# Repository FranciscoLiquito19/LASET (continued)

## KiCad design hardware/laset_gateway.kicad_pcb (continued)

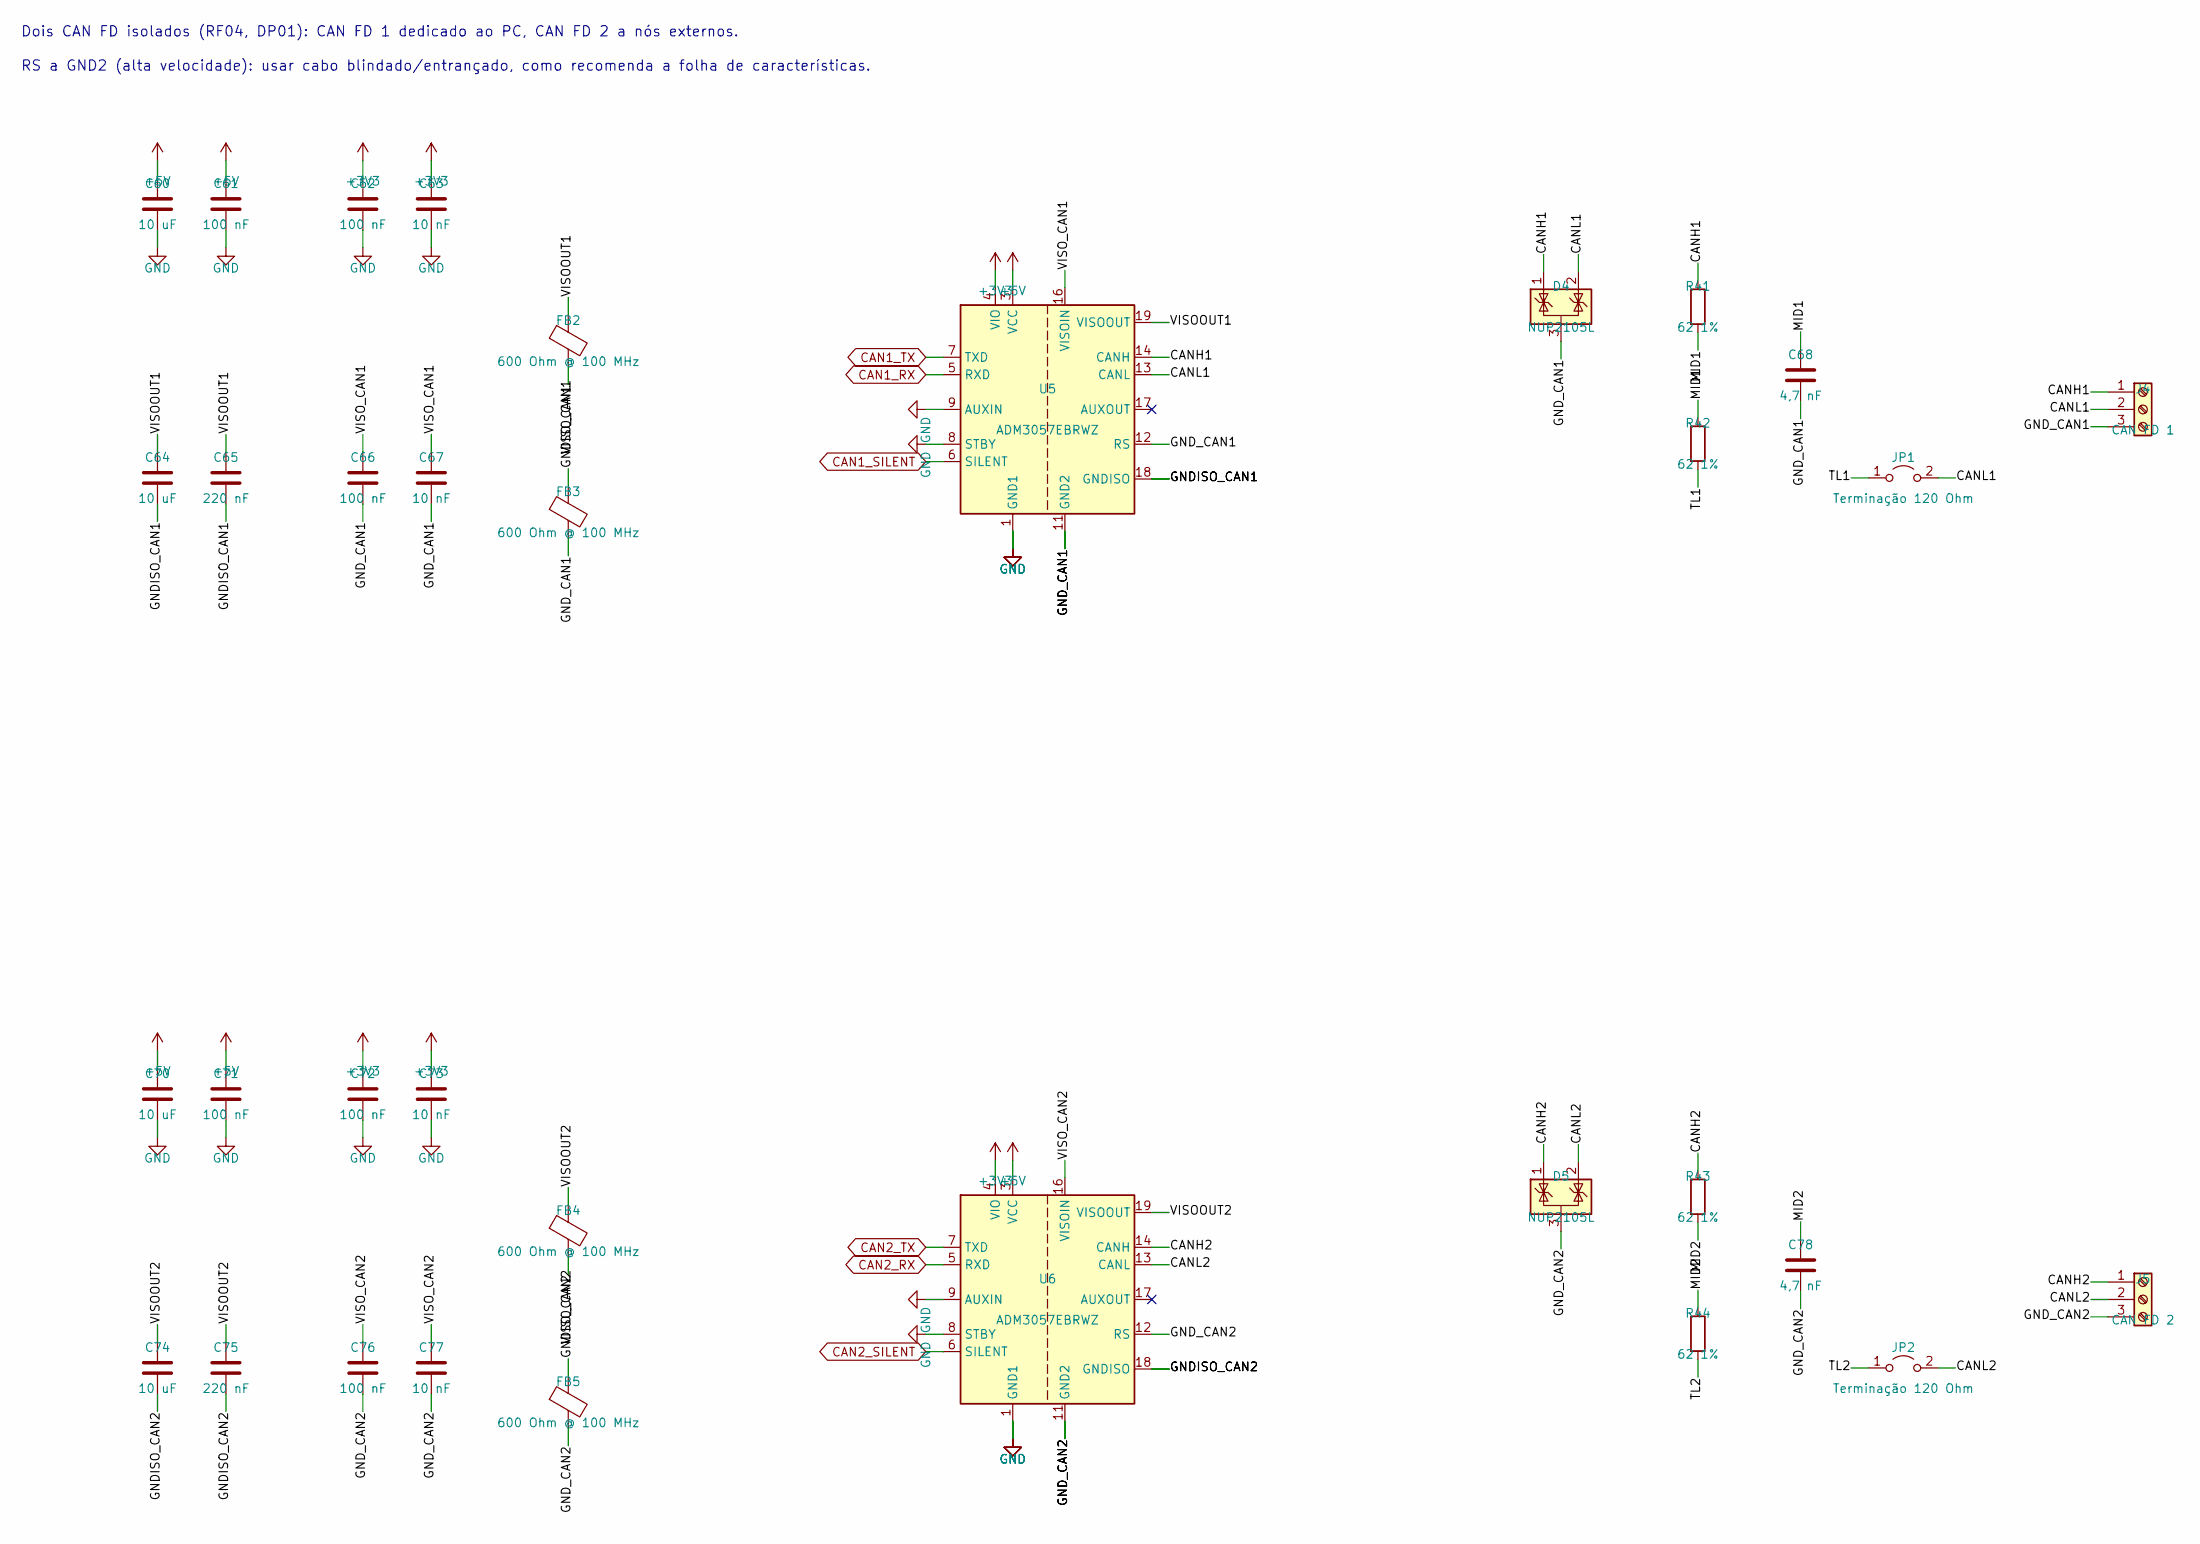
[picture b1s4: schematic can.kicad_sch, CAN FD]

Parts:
C60, C64, C70, C74: 10 uF; C_1206_3216Metric
C61, C62, C66, C71, C72, C76: 100 nF; C_0603_1608Metric
C63, C67, C73, C77: 10 nF; C_0603_1608Metric
C65, C75: 220 nF; C_0603_1608Metric
C68, C78: 4,7 nF; C_0603_1608Metric
D4, D5: NUP2105L; SOT-23
FB2, FB3, FB4, FB5: 600 Ohm @ 100 MHz; L_0603_1608Metric
J4: CAN FD 1; TerminalBlock_Phoenix_MKDS-1,5-3_1x03_P5.00mm_Horizontal
J5: CAN FD 2; TerminalBlock_Phoenix_MKDS-1,5-3_1x03_P5.00mm_Horizontal
JP1, JP2: Terminação 120 Ohm; PinHeader_1x02_P2.54mm_Vertical
R41, R42, R43, R44: 62 1%; R_0603_1608Metric
U5, U6: ADM3057EBRWZ; SOIC-20W_7.5x12.8mm_P1.27mm

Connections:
+3V3: C62.1, C63.1, C72.1, C73.1, U5.4 (VIO), U6.4 (VIO); also elsewhere on the board
+5V: C60.1, C61.1, C70.1, C71.1, U5.3 (VCC), U6.3 (VCC); also elsewhere on the board
/CAN FD/CANH1: D4.1 (K), J4.1, R41.1, U5.14 (CANH)
/CAN FD/CANH2: D5.1 (K), J5.1, R43.1, U6.14 (CANH)
/CAN FD/CANL1: D4.2 (K), J4.2, JP1.2 (B), U5.13 (CANL)
/CAN FD/CANL2: D5.2 (K), J5.2, JP2.2 (B), U6.13 (CANL)
/CAN FD/GNDISO_CAN1: C64.2, C65.2, FB3.1, U5.18 (GNDISO), U5.20 (GNDISO)
/CAN FD/GNDISO_CAN2: C74.2, C75.2, FB5.1, U6.18 (GNDISO), U6.20 (GNDISO)
/CAN FD/GND_CAN1: C66.2, C67.2, C68.2, D4.3 (A), FB3.2, J4.3, U5.11 (GND2), U5.12 (RS), U5.15 (GND2)
/CAN FD/GND_CAN2: C76.2, C77.2, C78.2, D5.3 (A), FB5.2, J5.3, U6.11 (GND2), U6.12 (RS), U6.15 (GND2)
/CAN FD/MID1: C68.1, R41.2, R42.1
/CAN FD/MID2: C78.1, R43.2, R44.1
/CAN FD/TL1: JP1.1 (A), R42.2
/CAN FD/TL2: JP2.1 (A), R44.2
/CAN FD/VISOOUT1: C64.1, C65.1, FB2.1, U5.19 (VISOOUT)
/CAN FD/VISOOUT2: C74.1, C75.1, FB4.1, U6.19 (VISOOUT)
/CAN FD/VISO_CAN1: C66.1, C67.1, FB2.2, U5.16 (VISOIN)
/CAN FD/VISO_CAN2: C76.1, C77.1, FB4.2, U6.16 (VISOIN)
CAN1_RX: U5.5 (RXD); also elsewhere on the board
CAN1_SILENT: U5.6 (SILENT); also elsewhere on the board
CAN1_TX: U5.7 (TXD); also elsewhere on the board
CAN2_RX: U6.5 (RXD); also elsewhere on the board
CAN2_SILENT: U6.6 (SILENT); also elsewhere on the board
CAN2_TX: U6.7 (TXD); also elsewhere on the board
GND: C60.2, C61.2, C62.2, C63.2, C70.2, C71.2, C72.2, C73.2, U5.1 (GND1), U5.2 (GND1), U5.8 (STBY), U5.9 (AUXIN), U5.10 (GND1), U6.1 (GND1), U6.2 (GND1), U6.8 (STBY), U6.9 (AUXIN), U6.10 (GND1); also elsewhere on the board

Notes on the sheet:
Dois CAN FD isolados (RF04, DP01): CAN FD 1 dedicado ao PC, CAN FD 2 a nós externos.
RS a GND2 (alta velocidade): usar cabo blindado/entrançado, como recomenda a folha de características.

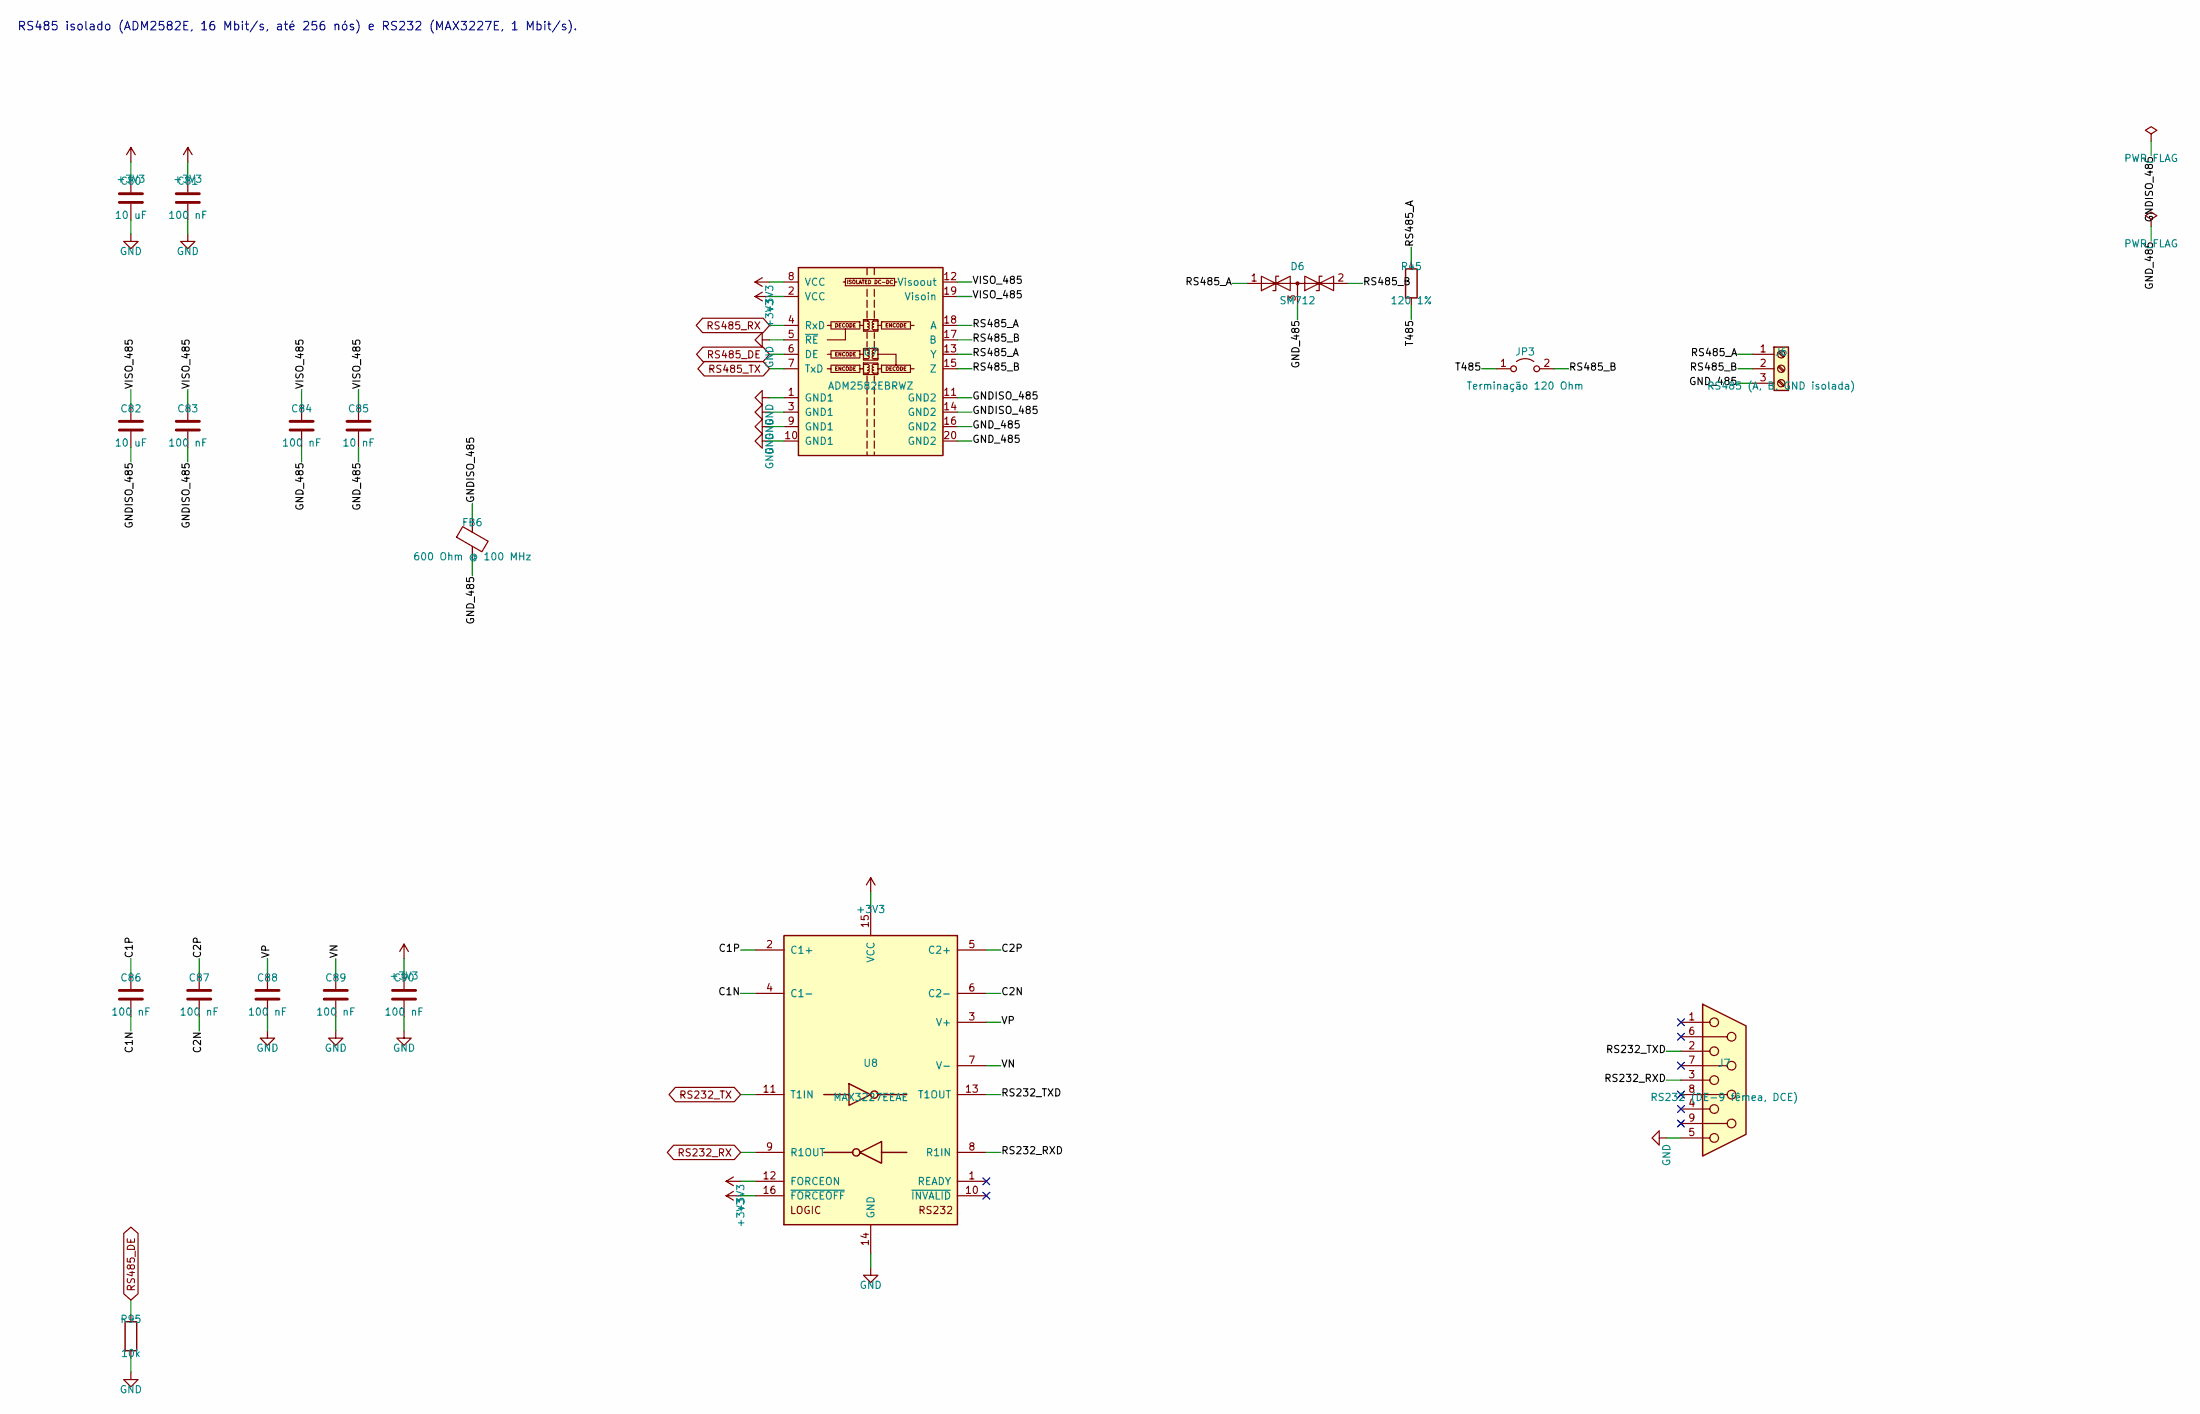
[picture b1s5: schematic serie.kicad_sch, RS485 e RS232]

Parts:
C80, C82: 10 uF; C_1206_3216Metric
C81, C83, C84, C86, C87, C88, C89, C90: 100 nF; C_0603_1608Metric
C85: 10 nF; C_0603_1608Metric
D6: SM712; SOT-23
FB6: 600 Ohm @ 100 MHz; L_0603_1608Metric
J6: RS485 (A, B, GND isolada); TerminalBlock_Phoenix_MKDS-1,5-3_1x03_P5.00mm_Horizontal
J7: RS232 (DE-9 fêmea, DCE); DSUB-9_Female_Horizontal_P2.77x2.84mm_EdgePinOffset7.70mm_H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
JP3: Terminação 120 Ohm; PinHeader_1x02_P2.54mm_Vertical
R45: 120 1%; R_0603_1608Metric
R95: 10k; R_0603_1608Metric
U7: ADM2582EBRWZ; SOIC-20W_7.5x12.8mm_P1.27mm
U8: MAX3227EEAE; SSOP-16_5.3x6.2mm_P0.65mm

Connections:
+3V3: C80.1, C81.1, C90.1, U7.2 (VCC), U7.8 (VCC), U8.12 (FORCEON), U8.15 (VCC), U8.16 (~FORCEOFF); also elsewhere on the board
/RS485 e RS232/C1N: C86.2, U8.4 (C1-)
/RS485 e RS232/C1P: C86.1, U8.2 (C1+)
/RS485 e RS232/C2N: C87.2, U8.6 (C2-)
/RS485 e RS232/C2P: C87.1, U8.5 (C2+)
/RS485 e RS232/GNDISO_485: C82.2, C83.2, FB6.1, U7.11 (GND2), U7.14 (GND2)
/RS485 e RS232/GND_485: C84.2, C85.2, D6.3 (common), FB6.2, J6.3, U7.16 (GND2), U7.20 (GND2)
/RS485 e RS232/RS232_RXD: J7.3, U8.8 (R1IN)
/RS485 e RS232/RS232_TXD: J7.2, U8.13 (T1OUT)
/RS485 e RS232/RS485_A: D6.1 (A1), J6.1, R45.1, U7.13 (Y), U7.18 (A)
/RS485 e RS232/RS485_B: D6.2 (A2), J6.2, JP3.2 (B), U7.15 (Z), U7.17 (B)
/RS485 e RS232/T485: JP3.1 (A), R45.2
/RS485 e RS232/VISO_485: C82.1, C83.1, C84.1, C85.1, U7.12 (Visoout), U7.19 (Visoin)
/RS485 e RS232/VN: C89.1, U8.7 (V-)
/RS485 e RS232/VP: C88.1, U8.3 (V+)
GND: C80.2, C81.2, C88.2, C89.2, C90.2, J7.5, R95.2, U7.1 (GND1), U7.3 (GND1), U7.5 (~RE), U7.9 (GND1), U7.10 (GND1), U8.14 (GND); also elsewhere on the board
RS232_RX: U8.9 (R1OUT); also elsewhere on the board
RS232_TX: U8.11 (T1IN); also elsewhere on the board
RS485_DE: R95.1, U7.6 (DE); also elsewhere on the board
RS485_RX: U7.4 (RxD); also elsewhere on the board
RS485_TX: U7.7 (TxD); also elsewhere on the board

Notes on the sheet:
RS485 isolado (ADM2582E, 16 Mbit/s, até 256 nós) e RS232 (MAX3227E, 1 Mbit/s).

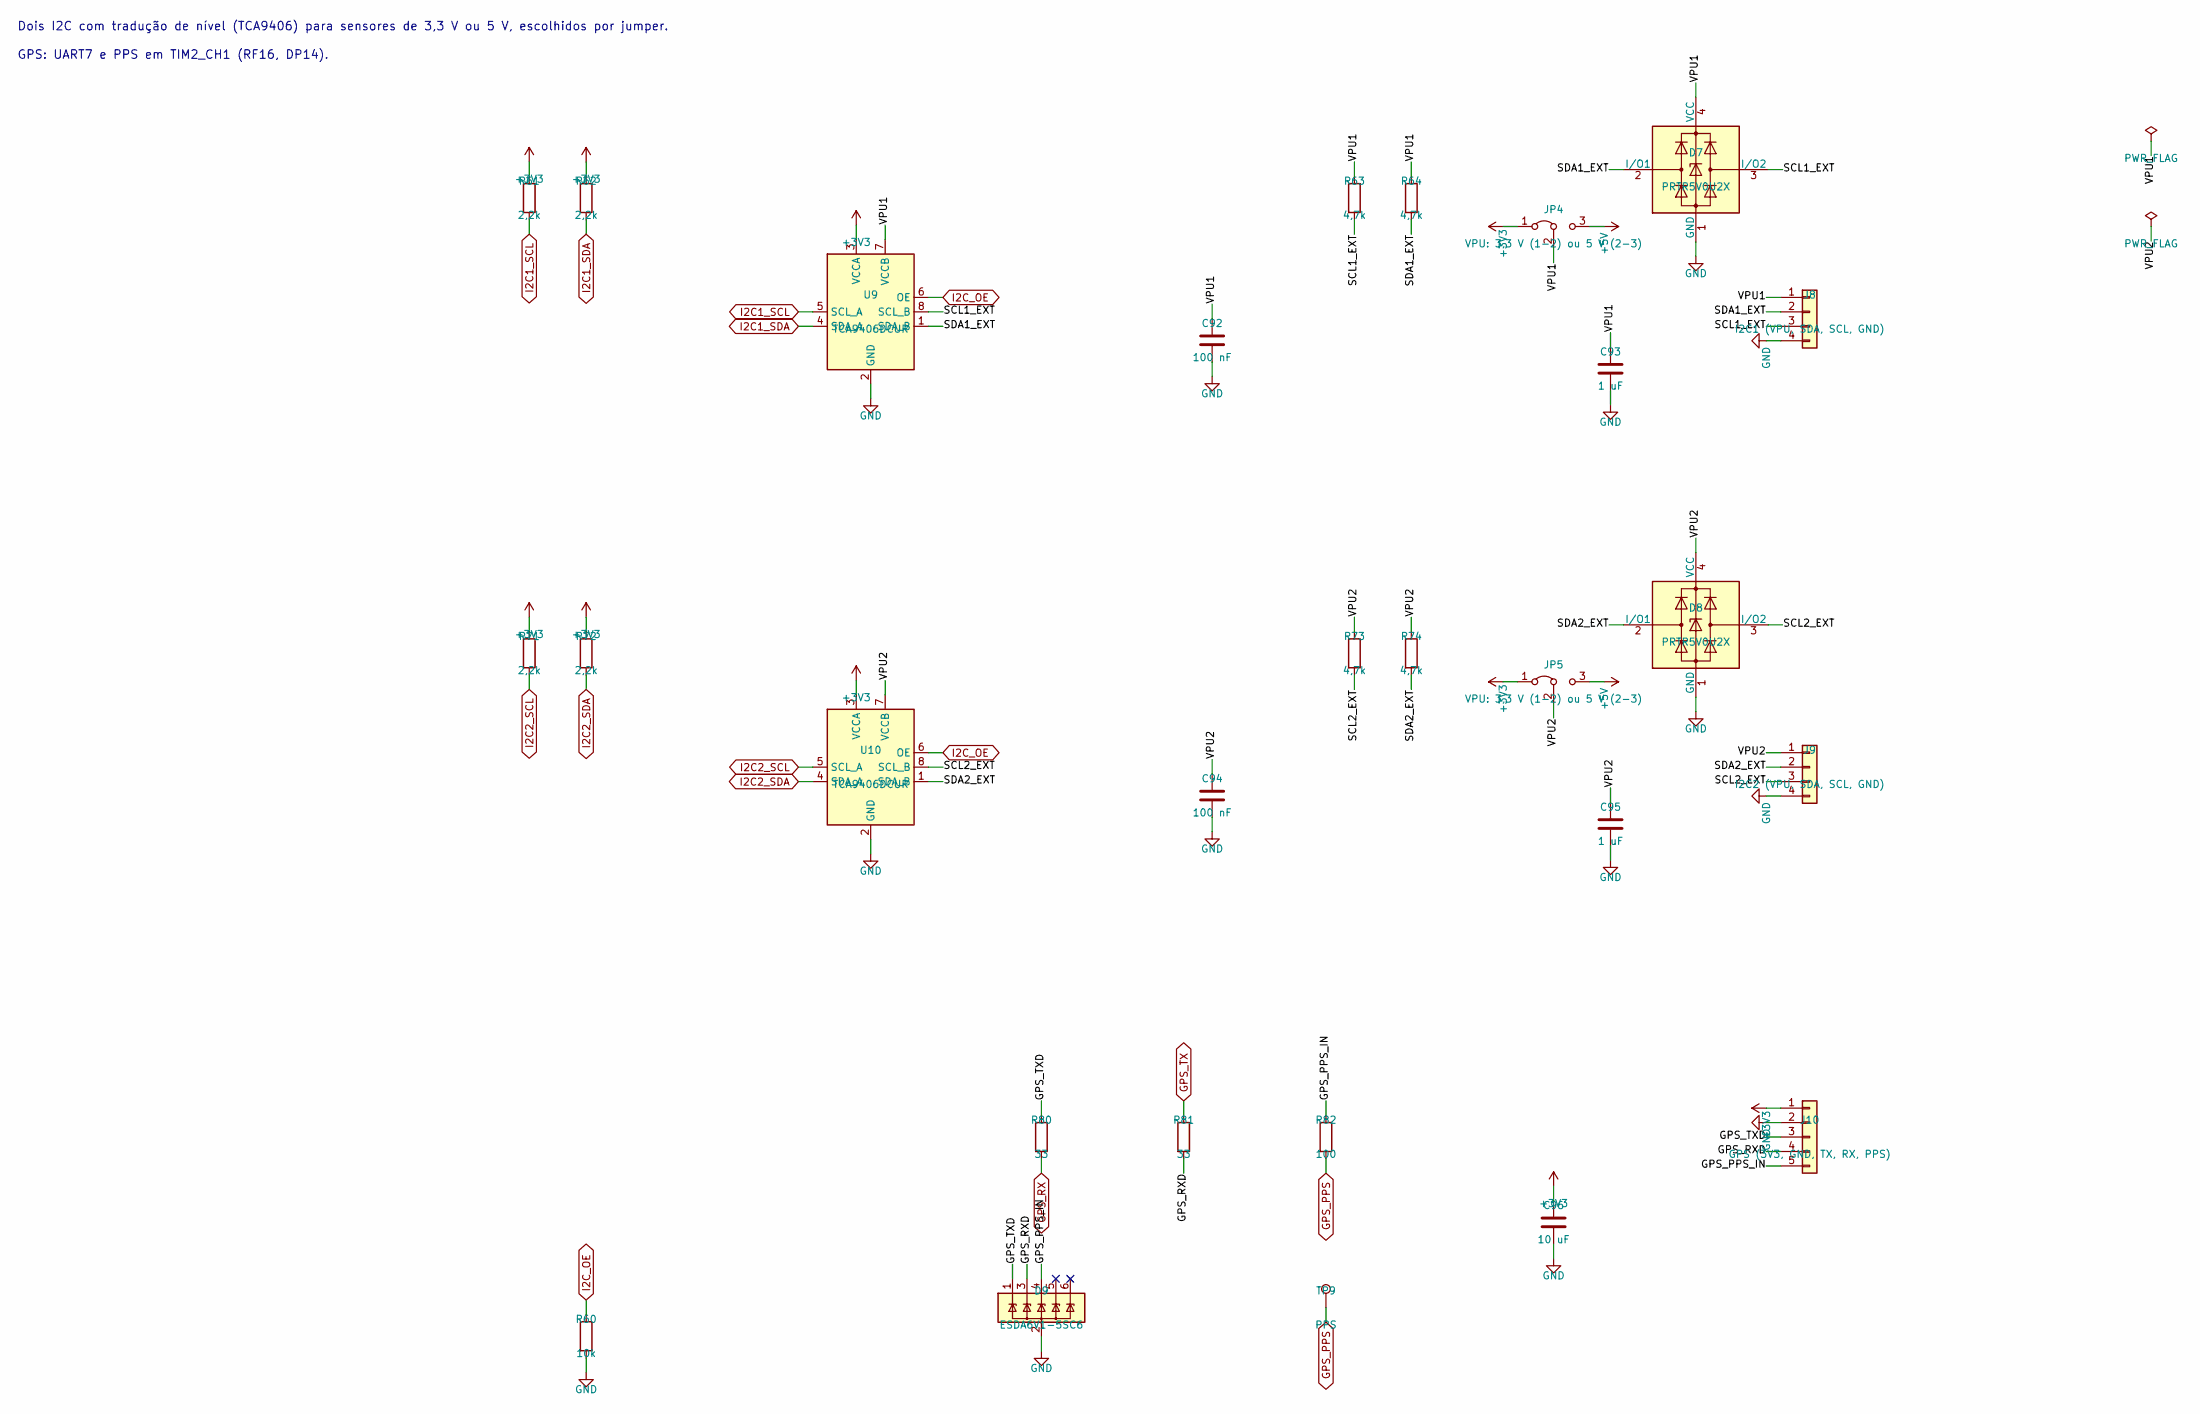
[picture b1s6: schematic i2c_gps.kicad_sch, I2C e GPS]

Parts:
C92, C94: 100 nF; C_0603_1608Metric
C93, C95: 1 uF; C_0603_1608Metric
C96: 10 uF; C_1206_3216Metric
D7, D8: PRTR5V0U2X; SOT-143
D9: ESDA6V1-5SC6; SOT-23-6
J8: I2C1 (VPU, SDA, SCL, GND); JST_PH_B4B-PH-K_1x04_P2.00mm_Vertical
J9: I2C2 (VPU, SDA, SCL, GND); JST_PH_B4B-PH-K_1x04_P2.00mm_Vertical
J10: GPS (3V3, GND, TX, RX, PPS); JST_PH_B5B-PH-K_1x05_P2.00mm_Vertical
JP4, JP5: VPU: 3,3 V (1-2) ou 5 V (2-3); PinHeader_1x03_P2.54mm_Vertical
R60: 10k; R_0603_1608Metric
R61, R62, R71, R72: 2,2k; R_0603_1608Metric
R63, R64, R73, R74: 4,7k; R_0603_1608Metric
R80, R81: 33; R_0603_1608Metric
R82: 100; R_0603_1608Metric
TP9: PPS; TestPoint_Pad_D1.5mm
U9, U10: TCA9406DCUR; VSSOP-8_2.3x2mm_P0.5mm

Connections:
+3V3: C96.1, J10.1, JP4.1 (A), JP5.1 (A), R61.1, R62.1, R71.1, R72.1, U9.3 (VCCA), U10.3 (VCCA); also elsewhere on the board
+5V: JP4.3 (B), JP5.3 (B); also elsewhere on the board
/I2C e GPS/GPS_PPS_IN: D9.4 (IO3), J10.5, R82.1
/I2C e GPS/GPS_RXD: D9.3 (IO2), J10.4, R81.2
/I2C e GPS/GPS_TXD: D9.1 (IO1), J10.3, R80.1
/I2C e GPS/SCL1_EXT: D7.3 (I/O2), J8.3, R63.2, U9.8 (SCL_B)
/I2C e GPS/SCL2_EXT: D8.3 (I/O2), J9.3, R73.2, U10.8 (SCL_B)
/I2C e GPS/SDA1_EXT: D7.2 (I/O1), J8.2, R64.2, U9.1 (SDA_B)
/I2C e GPS/SDA2_EXT: D8.2 (I/O1), J9.2, R74.2, U10.1 (SDA_B)
/I2C e GPS/VPU1: C92.1, C93.1, D7.4 (VCC), J8.1, JP4.2 (C), R63.1, R64.1, U9.7 (VCCB)
/I2C e GPS/VPU2: C94.1, C95.1, D8.4 (VCC), J9.1, JP5.2 (C), R73.1, R74.1, U10.7 (VCCB)
GND: C92.2, C93.2, C94.2, C95.2, C96.2, D7.1 (GND), D8.1 (GND), D9.2 (GND), J8.4, J9.4, J10.2, R60.2, U9.2 (GND), U10.2 (GND); also elsewhere on the board
GPS_PPS: R82.2, TP9.1; also elsewhere on the board
GPS_RX: R80.2; also elsewhere on the board
GPS_TX: R81.1; also elsewhere on the board
I2C1_SCL: R61.2, U9.5 (SCL_A); also elsewhere on the board
I2C1_SDA: R62.2, U9.4 (SDA_A); also elsewhere on the board
I2C2_SCL: R71.2, U10.5 (SCL_A); also elsewhere on the board
I2C2_SDA: R72.2, U10.4 (SDA_A); also elsewhere on the board
I2C_OE: R60.1, U9.6 (OE), U10.6 (OE); also elsewhere on the board

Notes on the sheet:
Dois I2C com tradução de nível (TCA9406) para sensores de 3,3 V ou 5 V, escolhidos por jumper.
GPS: UART7 e PPS em TIM2_CH1 (RF16, DP14).

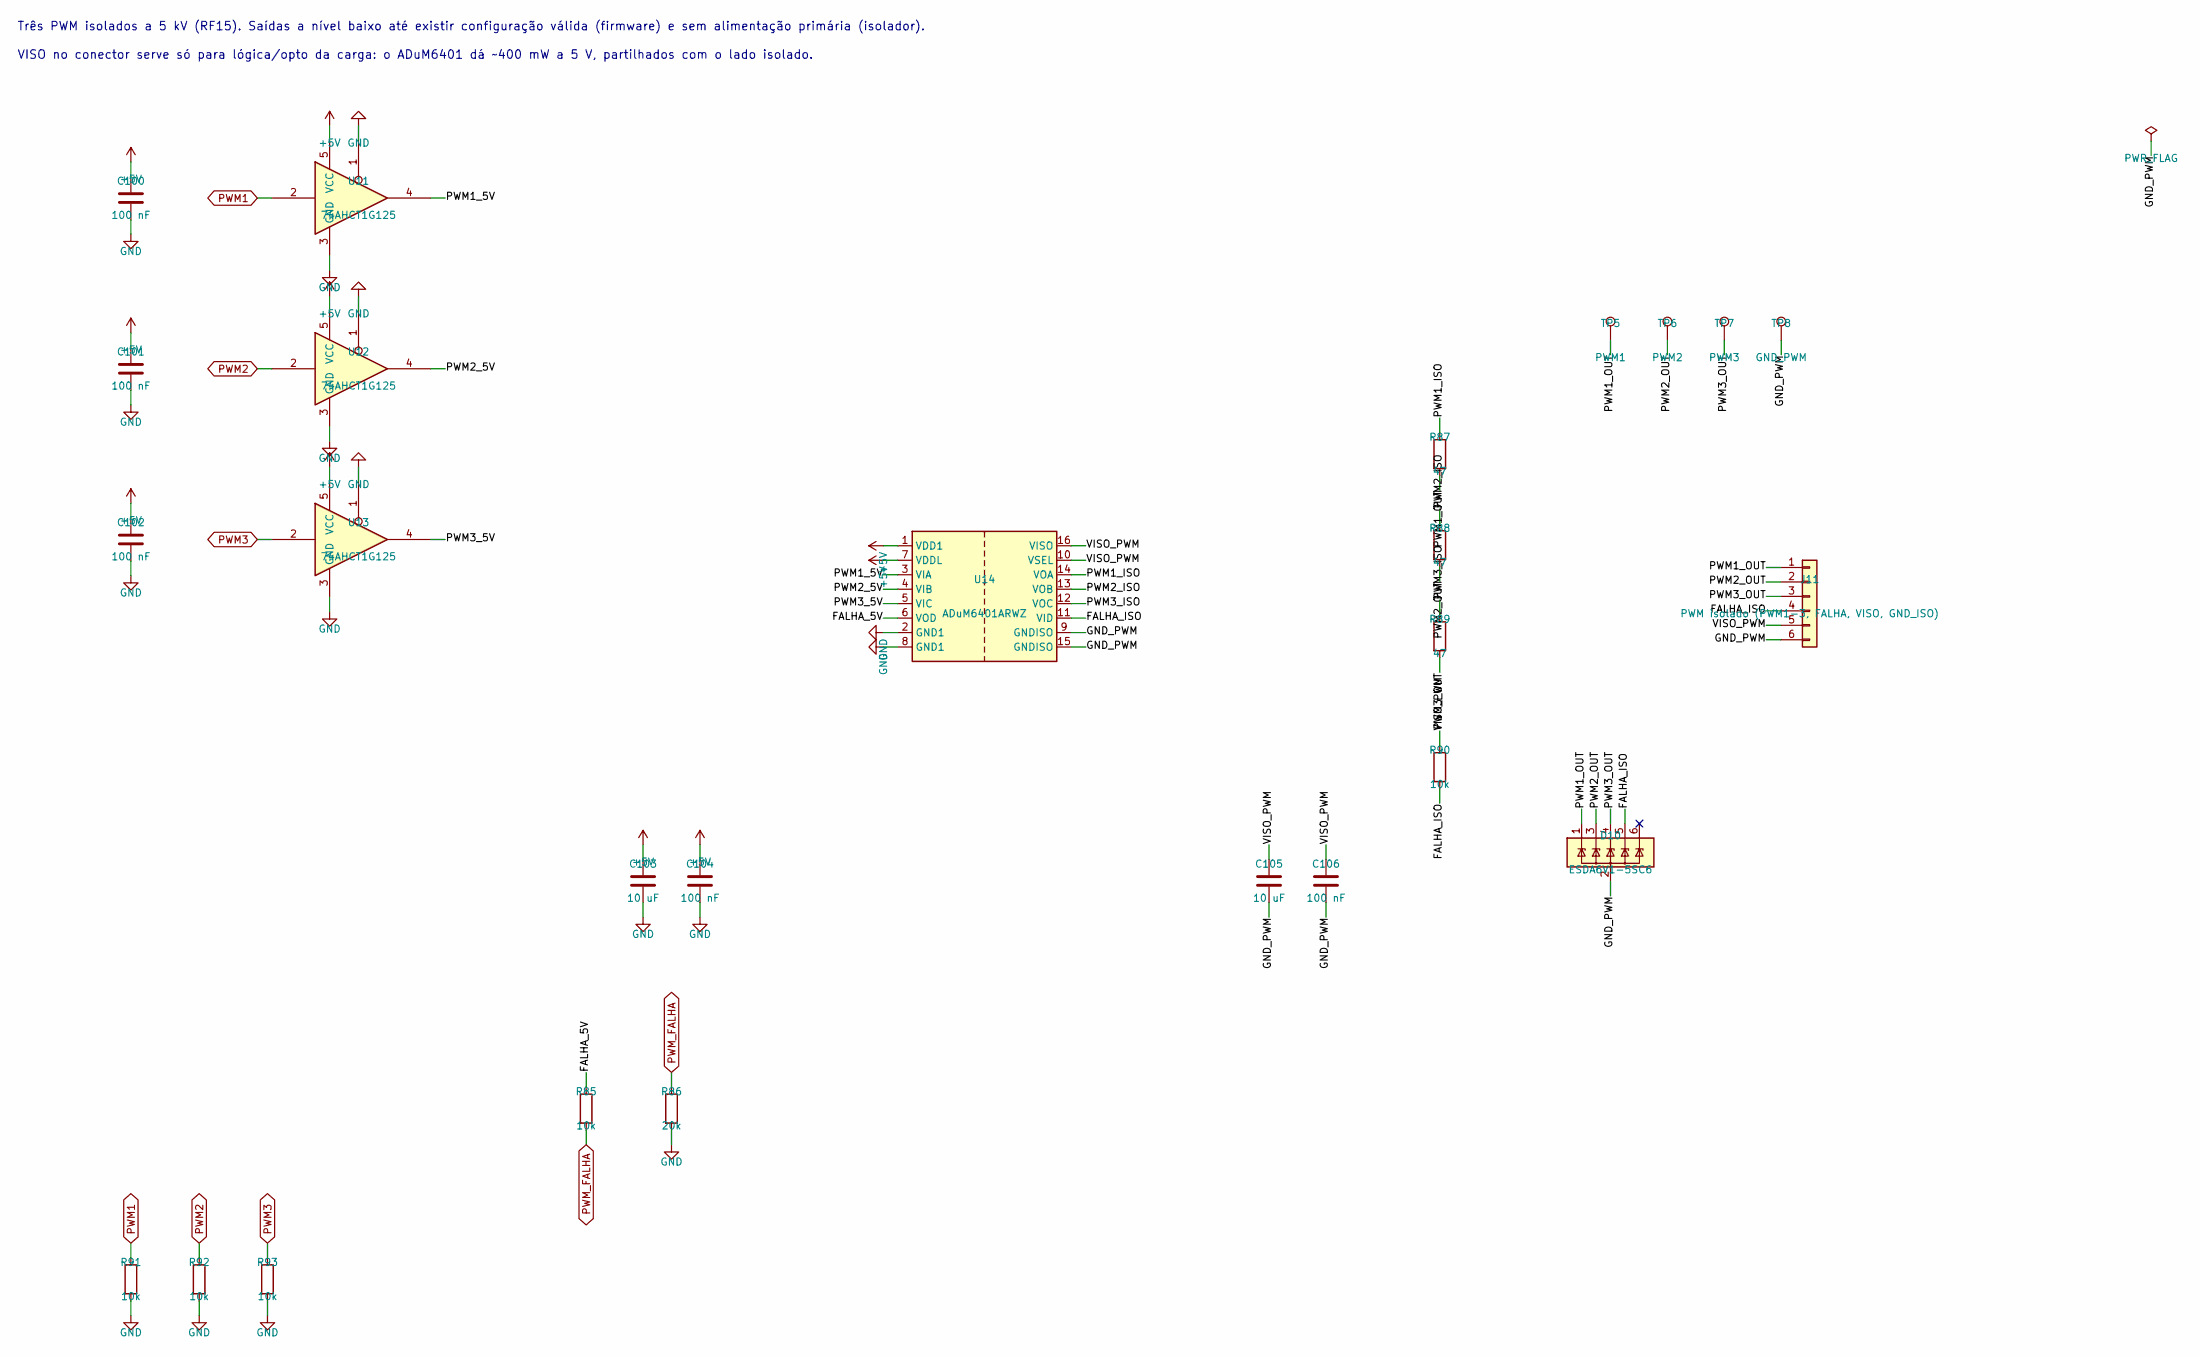
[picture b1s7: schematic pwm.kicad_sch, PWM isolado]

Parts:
C100, C101, C102, C104, C106: 100 nF; C_0603_1608Metric
C103, C105: 10 uF; C_1206_3216Metric
D10: ESDA6V1-5SC6; SOT-23-6
J11: PWM isolado (PWM1-3, FALHA, VISO, GND_ISO); JST_PH_B6B-PH-K_1x06_P2.00mm_Vertical
R85, R90, R91, R92, R93: 10k; R_0603_1608Metric
R86: 20k; R_0603_1608Metric
R87, R88, R89: 47; R_0603_1608Metric
TP5: PWM1; TestPoint_Pad_D1.5mm
TP6: PWM2; TestPoint_Pad_D1.5mm
TP7: PWM3; TestPoint_Pad_D1.5mm
TP8: GND_PWM; TestPoint_Pad_D1.5mm
U11, U12, U13: 74AHCT1G125; SOT-23-5
U14: ADuM6401ARWZ; SOIC-16W_7.5x10.3mm_P1.27mm

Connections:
+5V: C100.1, C101.1, C102.1, C103.1, C104.1, U11.5 (VCC), U12.5 (VCC), U13.5 (VCC), U14.1 (VDD1), U14.7 (VDDL); also elsewhere on the board
/PWM isolado/FALHA_5V: R85.1, U14.6 (VOD)
/PWM isolado/FALHA_ISO: D10.5 (IO4), J11.4, R90.2, U14.11 (VID)
/PWM isolado/GND_PWM: C105.2, C106.2, D10.2 (GND), J11.6, TP8.1, U14.9 (GNDISO), U14.15 (GNDISO)
/PWM isolado/PWM1_5V: U11.4, U14.3 (VIA)
/PWM isolado/PWM1_ISO: R87.1, U14.14 (VOA)
/PWM isolado/PWM1_OUT: D10.1 (IO1), J11.1, R87.2, TP5.1
/PWM isolado/PWM2_5V: U12.4, U14.4 (VIB)
/PWM isolado/PWM2_ISO: R88.1, U14.13 (VOB)
/PWM isolado/PWM2_OUT: D10.3 (IO2), J11.2, R88.2, TP6.1
/PWM isolado/PWM3_5V: U13.4, U14.5 (VIC)
/PWM isolado/PWM3_ISO: R89.1, U14.12 (VOC)
/PWM isolado/PWM3_OUT: D10.4 (IO3), J11.3, R89.2, TP7.1
/PWM isolado/VISO_PWM: C105.1, C106.1, J11.5, R90.1, U14.10 (VSEL), U14.16 (VISO)
GND: C100.2, C101.2, C102.2, C103.2, C104.2, R86.2, R91.2, R92.2, R93.2, U11.1, U11.3 (GND), U12.1, U12.3 (GND), U13.1, U13.3 (GND), U14.2 (GND1), U14.8 (GND1); also elsewhere on the board
PWM1: R91.1, U11.2; also elsewhere on the board
PWM2: R92.1, U12.2; also elsewhere on the board
PWM3: R93.1, U13.2; also elsewhere on the board
PWM_FALHA: R85.2, R86.1; also elsewhere on the board

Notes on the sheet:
Três PWM isolados a 5 kV (RF15). Saídas a nível baixo até existir configuração válida (firmware) e sem alimentação primária (isolador).
VISO no conector serve só para lógica/opto da carga: o ADuM6401 dá ~400 mW a 5 V, partilhados com o lado isolado.

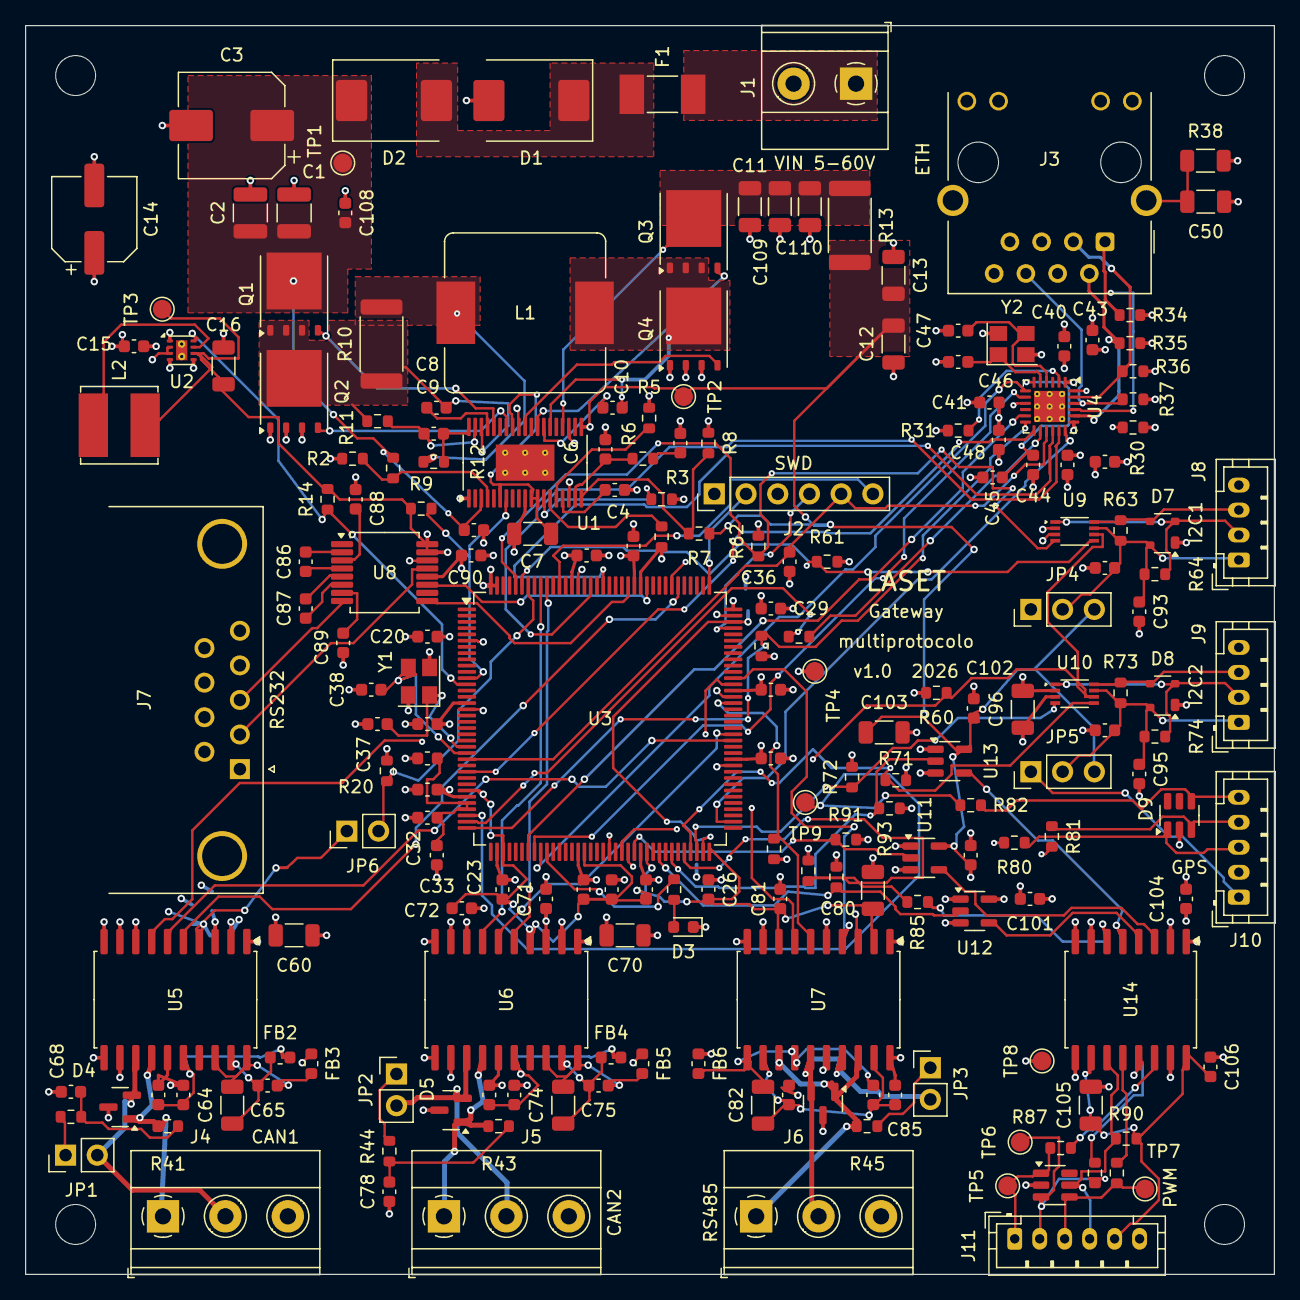
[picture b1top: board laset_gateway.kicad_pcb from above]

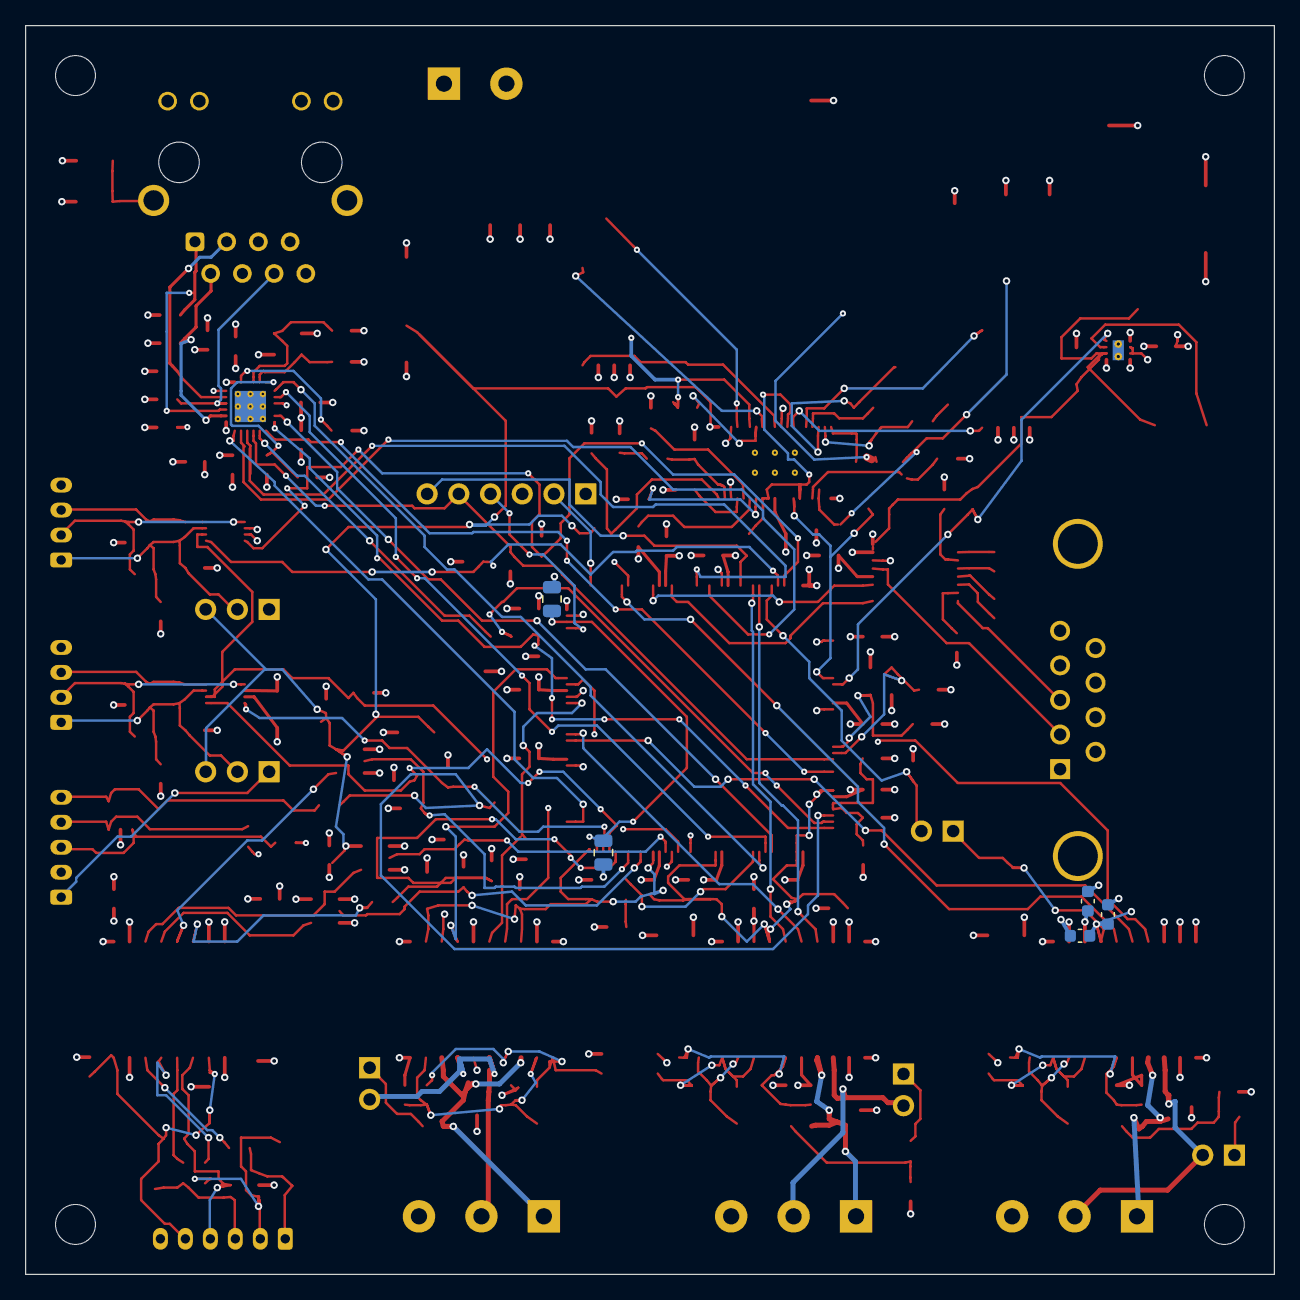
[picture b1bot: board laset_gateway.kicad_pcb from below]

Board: 4 copper layers, 100.0 x 100.0 mm, 212 parts (5 on the bottom side), 136 nets.

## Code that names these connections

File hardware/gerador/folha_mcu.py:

"""Folha 2: microcontrolador STM32H743ZIT6 (LQFP-144).

Atribuição de pinos (funções alternativas da folha de características DS12110 da ST;
o percurso Ethernet RMII é o mesmo da NUCLEO-H743ZI, o que permite reaproveitar o
projeto CubeMX da placa de avaliação):

  Ethernet RMII  PA1 REF_CLK, PA2 MDIO, PC1 MDC, PA7 CRS_DV, PC4 RXD0, PC5 RXD1,
                 PG11 TX_EN, PG13 TXD0, PB13 TXD1
  FDCAN1         PD0 RX, PD1 TX          SILENT do transceiver: PG2
  FDCAN2         PB5 RX, PB6 TX          SILENT do transceiver: PG3
  RS232 (USART2) PD5 TX, PD6 RX
  RS485 (USART6) PC6 TX, PC7 RX, PG8 DE (controlo automático do emissor)
  GPS (UART7)    PE8 TX, PE7 RX; PPS em PA0 = TIM2_CH1 (temporizador de 32 bits)
  I2C1           PB8 SCL, PB9 SDA
  I2C2           PB10 SCL, PB11 SDA (canto inferior direito, do lado dos conectores I2C)
  PWM (TIM1)     PE9 CH1, PE11 CH2, PE13 CH3; PE15 = TIM1_BKIN (falha isolada)
  SWD            PA13 SWDIO, PA14 SWCLK, PB3 SWO
  Estado         PB0 LED; PF2 PG_5V; PF3 PG_3V3
"""
from hw import Folha, simbolo, pinos
from comum import (R, C, FB, R0603, C0603, C0805, FB0603, LED0603, XTAL3225, JP2, desacoplamento)

MCU = 'MCU_ST_STM32H7:STM32H743ZITx'

PINOS = {
    # alimentação
    'VDD': '+3V3', 'VDD33_USB': '+3V3', 'VBAT': '+3V3', 'VSS': 'GND', 'VSSA': 'GND',
    # PDR_ON a VDD liga o supervisor interno (reset por queda de tensão), como na NUCLEO;
    # flutuante fica indefinido.
    'PDR_ON': '+3V3',
    'VDDA': '/VDDA', 'VREF+': '/VDDA', 'VCAP': '/VCAP', 'NRST': 'NRST', 'BOOT0': '/BOOT0',
    'PH0': '/OSC_IN', 'PH1': '/OSC_OUT',
    # Ethernet RMII
    'PA1': 'ETH_REF_CLK', 'PA2': 'ETH_MDIO', 'PC1': 'ETH_MDC', 'PA7': 'ETH_CRS_DV',
    'PC4': 'ETH_RXD0', 'PC5': 'ETH_RXD1', 'PG11': 'ETH_TX_EN', 'PG13': 'ETH_TXD0', 'PB13': 'ETH_TXD1',
    # CAN FD
    'PD0': 'CAN1_RX', 'PD1': 'CAN1_TX', 'PG2': 'CAN1_SILENT',
    'PB5': 'CAN2_RX', 'PB6': 'CAN2_TX', 'PG3': 'CAN2_SILENT',
    # série
    'PD5': 'RS232_TX', 'PD6': 'RS232_RX',
    'PC6': 'RS485_TX', 'PC7': 'RS485_RX', 'PG8': 'RS485_DE',
    # GPS
    'PE8': 'GPS_TX', 'PE7': 'GPS_RX', 'PA0': 'GPS_PPS',
    # I2C
    'PB8': 'I2C1_SCL', 'PB9': 'I2C1_SDA', 'PB10': 'I2C2_SCL', 'PB11': 'I2C2_SDA', 'PG0': 'I2C_OE',
    # PWM
    'PE9': 'PWM1', 'PE11': 'PWM2', 'PE13': 'PWM3', 'PE15': 'PWM_FALHA',
    # depuração e estado
    'PA13': '/SWDIO', 'PA14': '/SWCLK', 'PB3': '/SWO', 'PB0': '/LED',
    'PF2': 'PG_5V', 'PF3': 'PG_3V3',
}


def folha():
    f = Folha('Microcontrolador', 'mcu.kicad_sch', notas=[
        'STM32H743ZIT6 (DP03). Atribuição de pinos no cabeçalho de gerador/folha_mcu.py; os GPIO livres ficam marcados como não ligados.',
        'Condensadores de 100 nF junto a cada par VDD/VSS; VCAP com 2,2 uF de baixa ESR (< 100 mOhm) por pino.',
        'Cristal HSE de 25 MHz: condensadores de carga para C_L = 10 pF; ajustar se o cristal escolhido tiver outra C_L.',
    ])
    nomes = {p.name for p in pinos(simbolo(MCU))}
    for k in PINOS:
        assert k in nomes, k
    f.comp('U3', MCU, 'STM32H743ZIT6', 210, 150, PINOS, nc_resto=True)

    # Desacoplamento do domínio digital: um 100 nF por pino VDD + 4,7 uF de reserva
    refs = [f'C{20 + i}' for i in range(12)]
    desacoplamento(f, refs, ['100 nF'] * 11 + ['4,7 uF'], '+3V3', 'GND', 30, 40, passo=9)

    # VDDA e VREF+ filtrados
    f.comp('FB1', FB, '600 Ohm @ 100 MHz', 40, 80, {1: '+3V3', 2: '/VDDA'}, FB0603)
    f.comp('C32', C, '1 uF', 55, 80, {1: '/VDDA', 2: 'GND'}, C0603)
    f.comp('C33', C, '100 nF', 65, 80, {1: '/VDDA', 2: 'GND'}, C0603)

    # Regulador interno (VCAP)
    f.comp('C34', C, '2,2 uF (baixa ESR)', 40, 105, {1: '/VCAP', 2: 'GND'}, C0805)
    f.comp('C35', C, '2,2 uF (baixa ESR)', 52, 105, {1: '/VCAP', 2: 'GND'}, C0805)

    # Reset e arranque
    f.comp('C36', C, '100 nF', 40, 130, {1: 'NRST', 2: 'GND'}, C0603)
    f.comp('R20', R, '10k', 52, 130, {1: '/BOOT0', 2: 'GND'}, R0603)
    f.comp('JP6', 'Jumper:Jumper_2_Open', 'BOOT0 (fechar = bootloader)', 66, 145, {1: '+3V3', 2: '/BOOT0'}, JP2)

    # Oscilador HSE
    f.comp('Y1', 'Device:Crystal_GND24', '25 MHz (C_L 10 pF)', 60, 165, {1: '/OSC_IN', 3: '/OSC_OUT', 2: 'GND', 4: 'GND'}, XTAL3225)
    f.comp('C37', C, '15 pF', 40, 180, {1: '/OSC_IN', 2: 'GND'}, C0603)
    f.comp('C38', C, '15 pF', 80, 180, {1: '/OSC_OUT', 2: 'GND'}, C0603)

    # SWD
    # Mesma ordem do CN4 (SWD) do ST-LINK das placas NUCLEO: cabo direto de 6 vias
    f.comp('J2', 'Connector_Generic:Conn_01x06', 'SWD (CN4 da NUCLEO)', 340, 70, {
        1: '+3V3', 2: '/SWCLK', 3: 'GND', 4: '/SWDIO', 5: 'NRST', 6: '/SWO'},
        'Connector_PinHeader_2.54mm:PinHeader_1x06_P2.54mm_Vertical')

    # LED de estado
    f.comp('R21', R, '1k', 330, 130, {1: '/LED', 2: '/LED_A'}, R0603)
    f.comp('D3', 'Device:LED', 'Verde', 345, 130, {2: '/LED_A', 1: 'GND'}, LED0603)
    # PWR_FLAG: redes alimentadas por ferrite, resistência ou regulador interno (ERC)
    f.flag('/VDDA', 395, 40)
    return f
